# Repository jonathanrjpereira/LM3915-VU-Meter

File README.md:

# LM3915 VU Meter
An audio volume level indicator using the LM3915.

**Order PCB:**

## Electronic Components
| Qty | Component | Buy |
| ------------- | ------------- | ------------- |
| 1 | LM3915 |[AliExpress](http://s.click.aliexpress.com/e/b1RIKGYY) |
| 1 | LM386 |[AliExpress](http://s.click.aliexpress.com/e/cFr5ZTPS) |
| 1 | IC Holders |[AliExpress](http://s.click.aliexpress.com/e/cHvnfsrA) |
| 1 | Electret Condenser Microphone |[AliExpress](http://s.click.aliexpress.com/e/bSOOMYPe) |
| 1 | 10Ω, 1KΩ, 4.7K, 10KΩ Resistor |[AliExpress](http://s.click.aliexpress.com/e/bh4eqrQs) |
| 21 | 5mm LED |[AliExpress](http://s.click.aliexpress.com/e/wuFpLXS) |
| 1 | 2.2uF, 100uF Capacitor |[AliExpress](http://s.click.aliexpress.com/e/c9FHzl5W) |
| 2 | 10uF Capacitor |[AliExpress](http://s.click.aliexpress.com/e/c9FHzl5W) |
| 1 | 10nF, 47nF, 0.1uF Capacitor |[AliExpress](http://s.click.aliexpress.com/e/byQG0DZW) |
| 1 | 2 Pin Screw Terminal |[AliExpress](http://s.click.aliexpress.com/e/bj5UNUs0) |
| 1 | 3-Pin Male Header Pins |[AliExpress](http://s.click.aliexpress.com/e/bIN5SJXw) |
| 1 | 2-Pin Jumper Cap |[AliExpress](http://s.click.aliexpress.com/e/BqfIU7O) |
| 1 | 5VDC Adapter |[AliExpress](http://s.click.aliexpress.com/e/V0x0bms) |
| 1 | PCB |[AliExpress](http://s.click.aliexpress.com/e/dhgwzKY) |

| Tools | Buy |
|--|--|
|Soldering Iron|[AliExpress](http://s.click.aliexpress.com/e/E83bSJI) |
|Soldering Wire|[AliExpress](http://s.click.aliexpress.com/e/PdhB0nm) |
|Mini PCB Hand Drill + Bits|[AliExpress](http://s.click.aliexpress.com/e/b93tomjI) |
|Wire Cutter|[AliExpress](http://s.click.aliexpress.com/e/bHFL9vLi) |
|Wire Stripper|[AliExpress](http://s.click.aliexpress.com/e/4yJWedw) |
|Soldering Helping Hands|[AliExpress](http://s.click.aliexpress.com/e/cAQ2StNm) |

## LM3915

The LM3915 is a monolithic integrated circuit that senses analog voltage levels and drives ten LEDs,
providing a logarithmic 3 dB/step analog display. One pin changes the display from a bar graph to
a moving dot display.

The whole display system can operate from a single supply as low as 3V or as high as 25V.

**Pinout**

The DIP package of the LM3915 has 18 pins. Most pins are used as output pins that drive the LEDs while the rest of the pins used as power supply, reference configurations and IC control.

**LED Configuration**

LED current drive is regulated and programmable, eliminating the need for current limiting resistors. Hence the anodes of the LEDs are directly connected to VCC and the cathodes are connected to the LM3915. The LEDs turn ON when the driving pins of the LM3915 are set to LOW.

**Analog Voltage Reference**

The IC contains an adjustable voltage reference and an accurate ten-step voltage divider. Pins 6 and 4 are used to set the sensitivity range of the voltage divider. RHI sets the maximum voltage of the voltage divider and RLO sets the minimum voltage of the voltage divider. These pins can be connected to any voltage above 0V and 1.5V below VCC.

**Mode Select**

The LM3915 has two display modes: Bar Graph mode & Moving Dot mode.
In the Bar Graph mode, all the LEDs turn ON below a certain level. Hence if the input signal level is maximum, all the LEDs should turn ON. Whereas in Moving Dot mode only a single LED is turned ON at a time.
The mode is selected by configuring Pin 9. When Pin 9 is connected to VCC, it operates in the Bar Graph mode whereas if Pin 9 is left floating, the LM3915 operates in the Moving Dot mode.

**LED Current Programming and Setting the Internal Voltage Reference**

The reference is designed to be adjustable and develops a nominal 1.25V between the REF OUT (pin 7) and REF ADJ (pin 8) terminals.

Since we are using only one resistor (R1), VREF = 1.25V, which is more than 1.5V below VCC.

The LED current is calculated using the following formula:

Hence if an LED requires 3mA, we will need to set the value of R to 4.7KΩ.

**Voltage Divider Working**

The voltage divider consists of ten comparators. If the non-inverting terminal(+) voltage is higher than the inverting terminal(-) voltage, the comparator comparator output is driven HIGH. The inverting terminal are all connected to the Input Signal (Pin 5). The non-inverting(+) terminals are connected through a series of resistors which create larger and larger voltage dividers. The non-inverting(+) voltage on the first comparator will be the divider input voltage (RHI − RLO), while the non-inverting(+) voltage on the last comparator is 1/10th of that voltage. Hence in order to turn ON an LED, the analog Input Signal voltage must be greater than the divided input on a comparator. So a smaller signal voltage is required to turn on the first LED in comparison to any of the following.

## LM386
The LM386 is a power amplifier designed for use in low voltage consumer applications. The gain is internally set to 20 to keep external part count low, but the addition of an external resistor and capacitor between pins 1 and 8 will increase the gain to any value from 20 to 200.

The inputs are ground referenced while the output automatically biases to one-half the supply voltage.

**Circuit:**

The microphone is an electret type and requires a resistor to bias the capacitor connected to it. Some electret microphones also have an amplifier built-in, which also needs power. The larger the resistor from VCC the larger the voltage drop caused by the supply current, though for an unamplified electret the current is low and the resistor may be bigger.
A too small resistor will cause the signal to be attenuated. VCC is ground for AC signals and a small resistor will cause too much current to go that way. In this case the 10KΩ resistor R2 acts as the bias resistor.

The capacitor C3 is used is used to filter the DC noise that might be coupled along with the analog electrical signals.

The LM386 amplifies the audio signal picked up by the microphone. The gain of the LM386 is set to 200 by connecting a 10uF capacitor between pins 1 and 8.

The LM3915 is used as the LED driver. By setting the value of resistor R4 to 4.7KΩ, the LED drive current is regulated to 3mA. A total of 20 LED's are driven by the LM3915.

The jumper connected across the header pins JP2 are used to select the display mode: Either Bar Graph mode or Moving Dot mode.

Capacitor's C1 and C2 filter out any noise in the supply line and LED1 is used to indicate the power supply status.

You can **Order the PCB:** 

Or you can printout the [PDF file](https://github.com/jonathanrjpereira/LM3915-VU-Meter/blob/master/img/printable.pdf) and make your own PCB using the [Iron-on method]().

## Contributing🛠
Are you an engineer or hobbyist who has a great idea for a new feature in this project? Maybe you have a good idea for a bug fix? Feel free to grab our code & schematics from Github and tinker with it. Don't forget to smash ⭐️ & the Pull Request button.

[![alt text][1.1]][1] [![alt text][2.1]][2] [![alt text][3.1]][3]

[1.1]: https://github.com/jonathanrjpereira/Social-Media-README/blob/master/youtube.png (YouTube)
[2.1]: https://github.com/jonathanrjpereira/Social-Media-README/blob/master/instagram.png (Instagram)
[3.1]: https://github.com/jonathanrjpereira/Social-Media-README/blob/master/github.png (GitHub)

[1]: https://www.youtube.com/channel/UCRW-41O1vy98KKgJRQoYzdg
[2]: https://www.instagram.com/electroguruji/
[3]: https://github.com/jonathanrjpereira

**References:**
[LM3915 Datasheet](https://github.com/jonathanrjpereira/LM3915-VU-Meter/blob/master/img/LM3915.pdf)
[LM386 Datasheet](http://www.ti.com/lit/ds/symlink/lm386.pdf)
[Sparkfun](https://learn.sparkfun.com/tutorials/dotbar-display-driver-hookup-guide/introduction)

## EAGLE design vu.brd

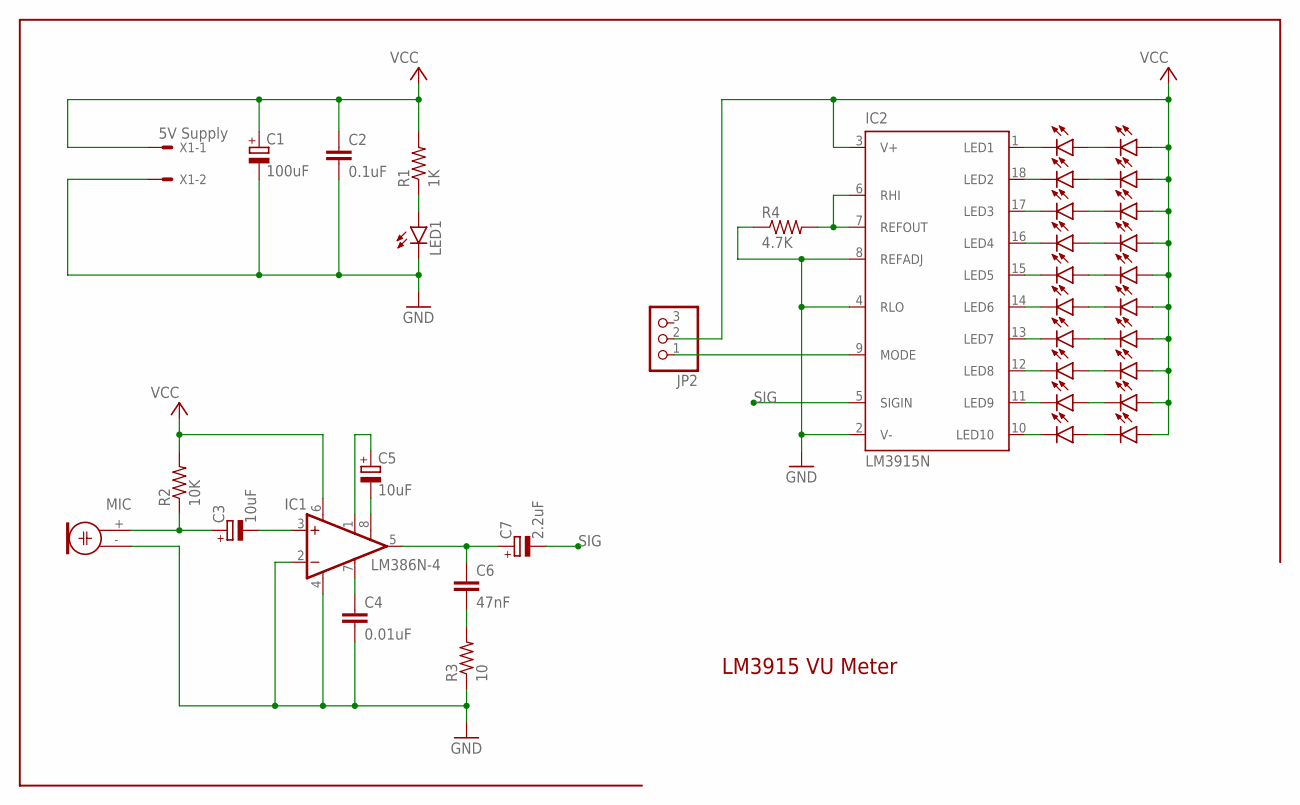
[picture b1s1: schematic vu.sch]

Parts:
C1: 100uF; E2,5-6
C2: 0.1uF; C025-050X050
C3, C5: 10uF; E2,5-6
C4: 0.01uF; C050-024X044
C6: 47nF; C025-050X050
C7: 2.2uF; E5-6
IC1: LM386N-4; DIL08
IC2: LM3915N; DIL18
JP2: PINHD-1X3; 1X03
LED1, LED2, LED3, LED4, LED5, LED6, LED7, LED8, LED9, LED10, LED11, LED12, LED13, LED14, LED15, LED16, LED17, LED18, LED19, LED20, LED21: LED5MM
MIC: ELECTRET; 9.7ELECTRET
R1: 1K; 0207/10
R2: 10K; 0207/10
R3: 10; 0207/10
R4: 4.7K; 0207/10
X1: 5V Supply; KK-156-2

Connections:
GND: C1.-, C2.2, C4.2, IC1.2 (-IN), IC1.4 (GND), IC2.2 (V-), IC2.4 (RLO), IC2.8 (REFADJ), LED1.K (C), MIC.- (1), R3.1, R4.1, X1.2
unnamed: C3.+, MIC.+ (2), R2.1
unnamed: C3.-, IC1.3 (+IN)
unnamed: C5.+, IC1.1 (GAIN)
unnamed: LED1.A, R1.1
unnamed: C5.-, IC1.8 (GAIN)
unnamed: C6.1, C7.+, IC1.5 (OUT)
unnamed: IC2.6 (RHI), IC2.7 (REFOUT), R4.2
unnamed: C6.2, R3.2
unnamed: C4.1, IC1.7 (BYPASS)
unnamed: IC2.1 (LED1), LED2.K (C)
unnamed: LED2.A, LED3.K (C)
unnamed: IC2.18 (LED2), LED4.K (C)
unnamed: LED4.A, LED5.K (C)
unnamed: IC2.17 (LED3), LED6.K (C)
unnamed: LED6.A, LED7.K (C)
unnamed: LED8.A, LED9.K (C)
unnamed: IC2.16 (LED4), LED8.K (C)
unnamed: IC2.15 (LED5), LED10.K (C)
unnamed: LED10.A, LED11.K (C)
unnamed: LED12.A, LED13.K (C)
unnamed: IC2.14 (LED6), LED12.K (C)
unnamed: IC2.13 (LED7), LED14.K (C)
unnamed: LED14.A, LED15.K (C)
unnamed: LED16.A, LED17.K (C)
unnamed: IC2.12 (LED8), LED16.K (C)
unnamed: IC2.11 (LED9), LED18.K (C)
unnamed: LED18.A, LED19.K (C)
unnamed: LED20.A, LED21.K (C)
unnamed: IC2.10 (LED10), LED20.K (C)
unnamed: IC2.9 (MODE), JP2.1
SIG: C7.-, IC2.5 (SIGIN)
VCC: C1.+, C2.1, IC1.6 (VS), IC2.3 (V+), JP2.2, LED3.A, LED5.A, LED7.A, LED9.A, LED11.A, LED13.A, LED15.A, LED17.A, LED19.A, LED21.A, R1.2, R2.2, X1.1

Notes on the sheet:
LM3915 VU Meter

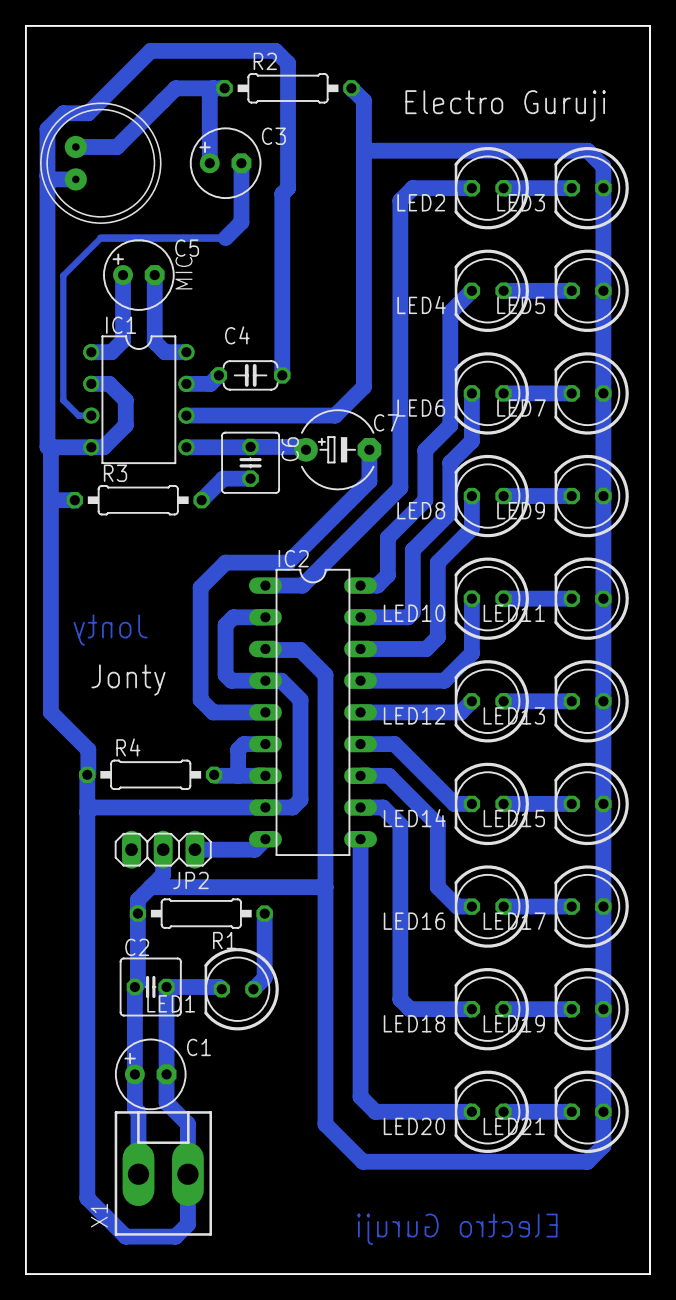
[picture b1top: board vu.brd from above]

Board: 2 copper layers, 50.0 x 100.0 mm, 37 parts (0 on the bottom side), 33 nets.

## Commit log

2019-04-09 Working
2019-04-09 Schematic
2019-04-09 Board
2019-04-09 Printable
2019-04-09 BOM - Tools
